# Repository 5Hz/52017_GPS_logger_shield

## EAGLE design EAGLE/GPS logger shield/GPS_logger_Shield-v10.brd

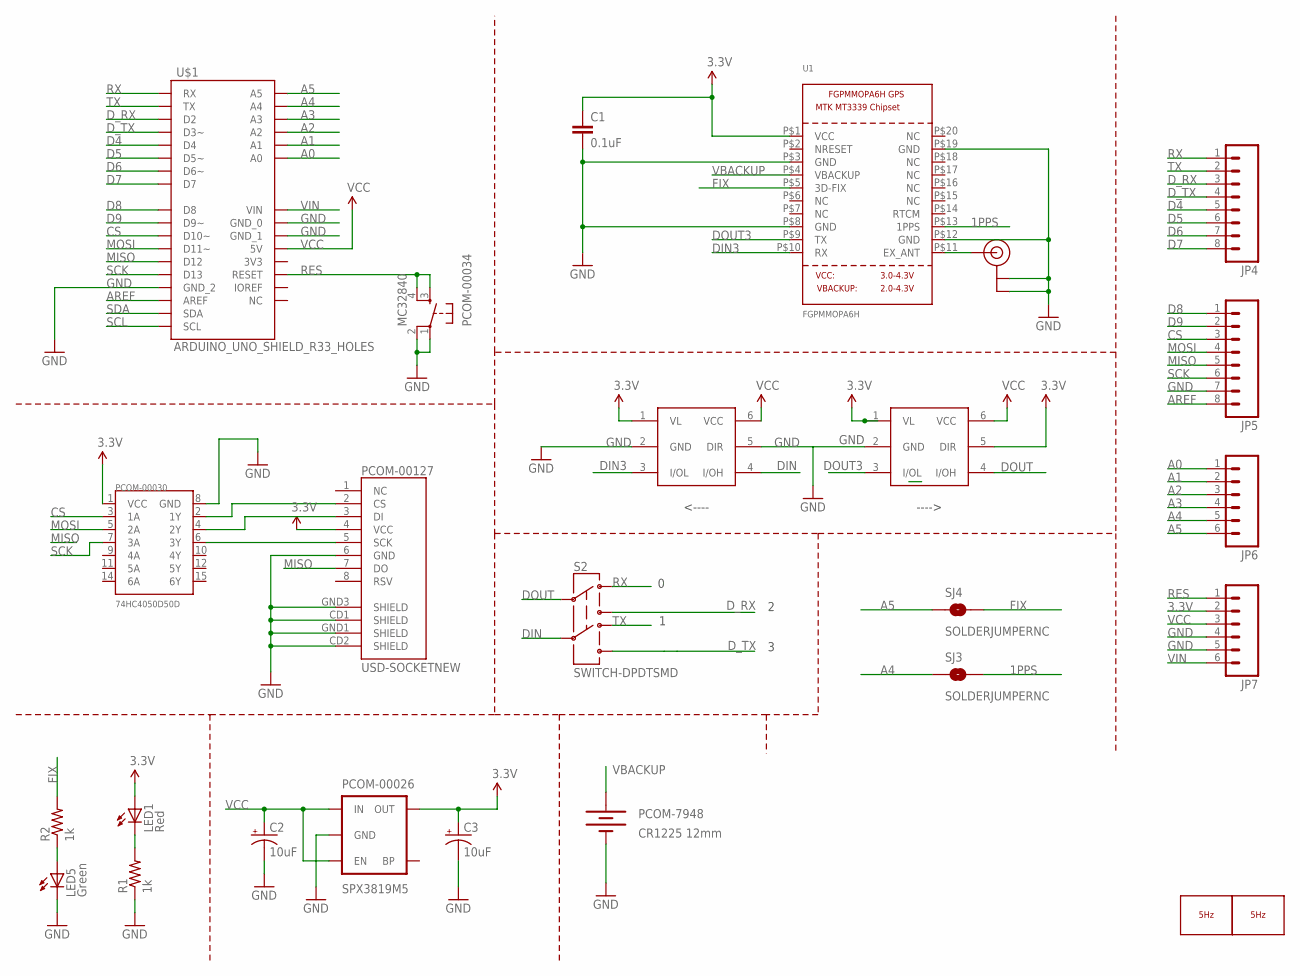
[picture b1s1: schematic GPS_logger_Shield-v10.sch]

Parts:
C1: 0.1uF; 0603-CAP
C2, C3: 10uF; EIA3216
JP4, JP5: M08; 1X08
JP6, JP7: M06SIP; 1X06
LED1: Red; LED-0603
LED5: Green; LED-0603
LOGO1: LOGO_5HZ_H_COOPER_15MM; 5HZ_LOGO_H_COOPER_15MM
LOGO2: LOGO_5HZ_MAIN_10MM; 5HZ_LOGO_MAIN_10MM
PCOM-00026: SPX3819M5; SOT23-5
PCOM-00030: 74HC4050D50D; SO016
PCOM-00034: MC32840; TACTILE_SWITCH_SMD
PCOM-00127: USD-SOCKETNEW; MICRO-SD-SOCKET-PP
PCOM-7948: CR1225 12mm; BATTCON_12MM_PTH
R1, R2: 1k; 0603-RES
S2: SWITCH-DPDTSMD; AYZ0202
SJ3, SJ4: SOLDERJUMPERNC; SJ_2S
U1: FGPMMOPA6H
U$1: ARDUINO_UNO_SHIELD_R33_HOLES; UNO_R3_SHIELD_3_HOLES_NO_SILK
U$7, U$8: MAX337; SOT-363
U$20: U.FL

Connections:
1PPS: SJ3.2, U1.P$13 (1PPS)
3.3V: C1.1, C3.A (+), JP7.2, LED1.A, PCOM-00026.5 (OUT), PCOM-00030.1 (VCC), PCOM-00127.4 (VCC), U1.P$1 (VCC), U$7.1 (VL), U$8.1 (VL), U$8.5 (DIR)
A0: JP6.1, U$1.A0
A1: JP6.2, U$1.A1
A2: JP6.3, U$1.A2
A3: JP6.4, U$1.A3
A4: JP6.5, SJ3.1, U$1.A4
A5: JP6.6, SJ4.1, U$1.A5
AREF: JP5.8, U$1.AREF
CS: JP5.3, PCOM-00030.3 (1A), U$1.D10 (D10~)
D4: JP4.5, U$1.D4
D5: JP4.6, U$1.D5 (D5~)
D6: JP4.7, U$1.D6 (D6~)
D7: JP4.8, U$1.D7
D8: JP5.1, U$1.D8
D9: JP5.2, U$1.D9 (D9~)
DIN: S2.5, U$7.4 (I/OH)
DIN3: U1.P$10 (RX), U$7.3 (I/OL)
DOUT: S2.2, U$8.4 (I/OH)
DOUT3: U1.P$9 (TX), U$8.3 (I/OL)
D_RX: JP4.3, S2.3, U$1.D2
D_TX: JP4.4, S2.6, U$1.D3 (D3~)
FIX: R2.2, SJ4.2, U1.P$5 (3D-FIX)
GND: C1.2, C2.C (-), C3.C (-), JP5.7, JP7.4, JP7.5, LED5.C, PCOM-00026.2 (GND), PCOM-00030.8 (GND), PCOM-00034.1, PCOM-00034.2, PCOM-00127.6 (GND), PCOM-00127.CD1 (SHIELD), PCOM-00127.CD2 (SHIELD), PCOM-00127.GND1 (SHIELD), PCOM-00127.GND3 (SHIELD), PCOM-7948.GND (-), R1.1, U1.P$3 (GND), U1.P$8 (GND), U1.P$12 (GND), U1.P$19 (GND), U$1.GND_0, U$1.GND_1, U$1.GND_2, U$7.2 (GND), U$7.5 (DIR), U$8.2 (GND), U$20.P$1 (GND), U$20.P$2 (GND)
MISO: JP5.5, PCOM-00127.7 (DO), U$1.D12
MOSI: JP5.4, PCOM-00030.5 (2A), U$1.D11 (D11~)
unnamed: PCOM-00030.4 (2Y), PCOM-00127.3 (DI)
unnamed: PCOM-00030.6 (3Y), PCOM-00127.5 (SCK)
unnamed: LED1.C, R1.2
unnamed: U1.P$11 (EX_ANT), U$20.P$3 (SIGNAL)
unnamed: LED5.A, R2.1
unnamed: PCOM-00030.2 (1Y), PCOM-00127.2 (CS)
RES: JP7.1, PCOM-00034.3, PCOM-00034.4, U$1.RES (RESET)
RX: JP4.1, S2.1, U$1.RX
SCK: JP5.6, PCOM-00030.7 (3A), U$1.D13
SCL: U$1.SCL
SDA: U$1.SDA
TX: JP4.2, S2.4, U$1.TX
VBACKUP: PCOM-7948.VCC@1 (+), U1.P$4 (VBACKUP)
VCC: C2.A (+), JP7.3, PCOM-00026.1 (IN), PCOM-00026.3 (EN), U$1.5V, U$7.6 (VCC), U$8.6 (VCC)
VIN: JP7.6, U$1.VIN

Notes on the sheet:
<----
---->

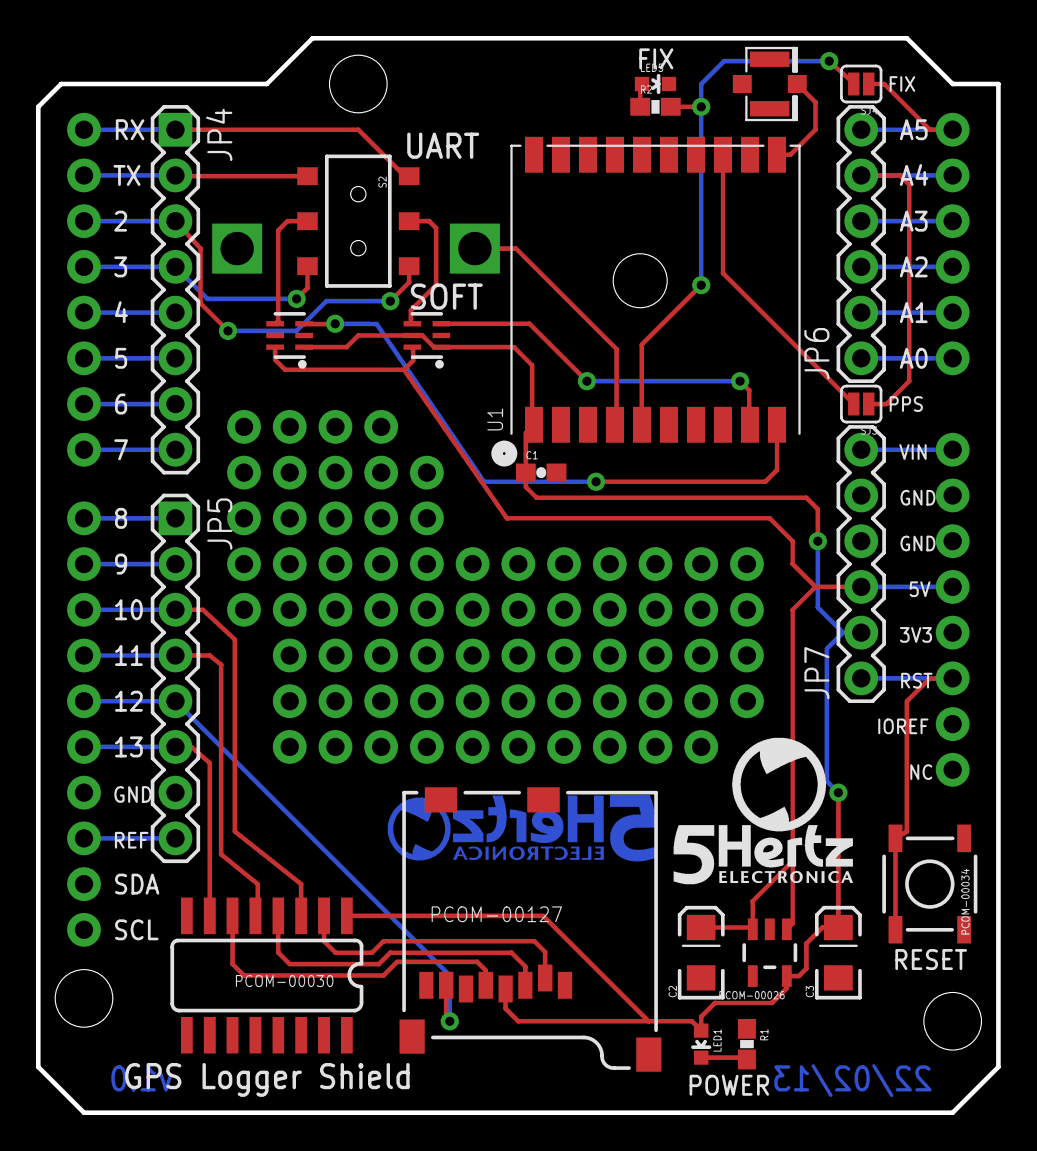
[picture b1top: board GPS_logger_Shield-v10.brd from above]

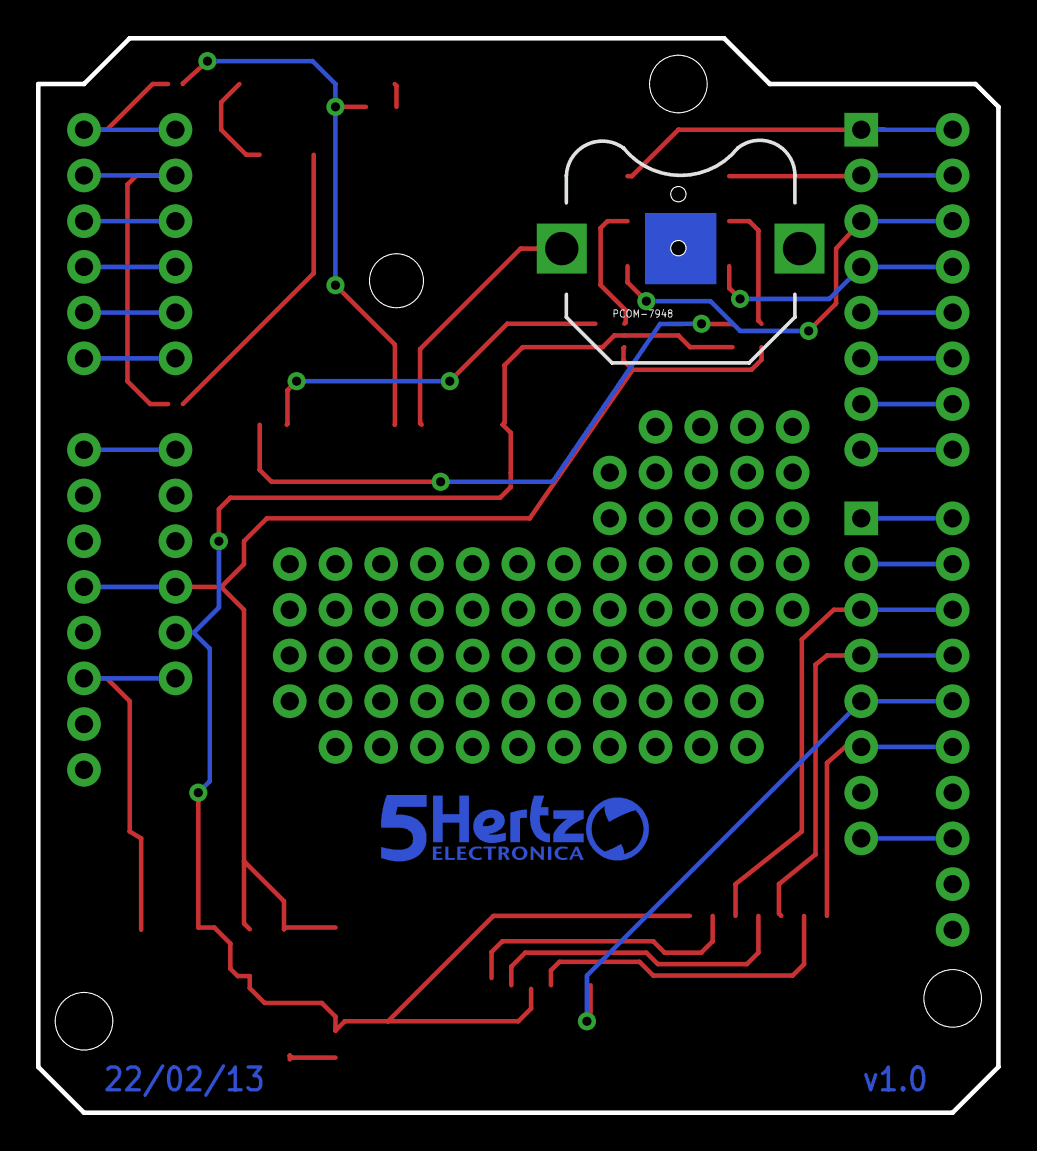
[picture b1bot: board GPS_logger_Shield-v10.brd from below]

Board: 2 copper layers, 53.3 x 59.7 mm, 26 parts (2 on the bottom side), 39 nets.

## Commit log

2014-01-14 creación
